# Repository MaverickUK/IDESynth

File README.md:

<h3 align="center">The sound of real mechanical drives, for retro PCs that use solid-state storage</h3>

<p align="center">

</p>

**Status:** Currently with beta testers with planned public release in early 2027

<!-- Demo: replace the photo with a short video of the board in a PC, spinning up and seeking (GIF in the README, linking to the MP4). -->

## Features

- **Real drives, sampled:** spin-up at power on, the idle hum, access clicks and crackles and the spindown when the power goes, played from the board's supercapacitor. Swap sample packs to change the drive.
- **Drives modelled from physics:** a pack can be a synthesised drive instead of recordings, from a 1985 stepper to a 2005 7,200 rpm drive, tuned by ear in the online [Drive Lab](https://maverickuk.github.io/IDESynth/drive-lab/).
- **Knows what the drive is doing:** from the motherboard's HDD LED, from your modern computer over USB or exactly from an [IDE Synth Bay](https://github.com/MaverickUK/IDESynthBay): file copies sound different from random access, and the head goes where the PC really reads.
- **On the board:** volume and balance on a knob, a button for the next pack, an RGB activity light and an optional OLED screen.

## Quick start

1. **Flash the firmware:** download `.uf2` from the [latest release](https://github.com/MaverickUK/IDESynth/releases/latest), hold **BOOT** and tap **RESET**, then drag the file onto the `RP2350` drive that appears.
2. **Fill a microSD card:** put each sample pack in its own folder under `/samples` (packs are in [HDDSynth_Samples](https://github.com/MaverickUK/HDDSynth_Samples)) and put the card in the board.
3. **Fit it:** connect the motherboard's HDD LED header to the board's HDD LED input and power
4. **Turn the PC on:** the drive spins up. Press the action button for the next pack.

## Documentation

| Page | What it covers |
|---|---|
| [SD card setup](docs/sd-card.md) | Sample packs, WAV formats, `pack.json` and every `settings.json` key |
| [Synthesised drives](docs/modelled-drives.md) | `drive.json`: synthesised drives, presets and every parameter |
| [Controls, lights and screen](docs/controls.md) | The rotary encoder and action button, beeps and LED colours, the OLED, editing the card over USB |
| [The IDE Synth Bay link](docs/link.md) | Wiring and what the drive tells the synth: sequential transfers, head positions, its timing |
| [Companion app and protocol](docs/companion.md) | Your computer's disk activity over USB, and the serial sentences |
| [The hardware](docs/hardware.md) | The MK5 board, mounting, and the KiCad files |
| [How it works](docs/architecture.md) | The two cores, where each sound plays from, power loss |
| [Building and flashing](docs/building.md) | Building it yourself, tests, the serial console, versioning |
| [History](docs/history.md) | From breadboard to MK5, with the early videos |
| [Changelog](firmware/CHANGELOG.md) | Every release |

## The Synth family

- **IDE Synth** (this one): plays the sound of hard drives and optical drives, real drives sampled or modelled from physics, in step with the Bay
- [IDE Synth Bay](https://github.com/MaverickUK/IDESynthBay): an IDE hard disk and CD-ROM drive served from a microSD card, telling the IDE Synth exactly what it does
- [FDD Synth Duo](https://github.com/MaverickUK/FDDSynthDuo): two floppy drives served from a microSD card, with real drive sounds
- [SynthMinder](https://github.com/MaverickUK/SynthMinder): the synth controller for DOS, changing discs, sound packs and the volume from the PC they're fitted to
- [GameMinder](https://github.com/MaverickUK/GameMinder): the games launcher for DOS, which browses, launches and keeps track of your DOS games
- [HDDSynth_Samples](https://github.com/MaverickUK/HDDSynth_Samples): the sample packs

## Licence and credits

- **Software and firmware:** [GNU GPL v3.0](LICENSE).
- **Hardware designs** (schematics, PCB files, BOM): [CC BY-NC-SA 4.0](LICENSE-HARDWARE), free for personal, non-commercial use and changes; commercial use needs my permission.

Inspired by the [HDD Clicker](https://www.serdashop.com/HDDClicker). Thanks to [Ian Scott of PicoGUS](https://picog.us/) for sharing his knowledge of the Pico on the ISA bus, [Marten Electric](https://www.martenelectric.cz/) for their ISA prototyping boards, and [PCBWay](https://www.pcbway.com) for making and assembling the prototypes.

Peter Bridger · [strifestreams.com/hddsynth](https://www.strifestreams.com/hddsynth)

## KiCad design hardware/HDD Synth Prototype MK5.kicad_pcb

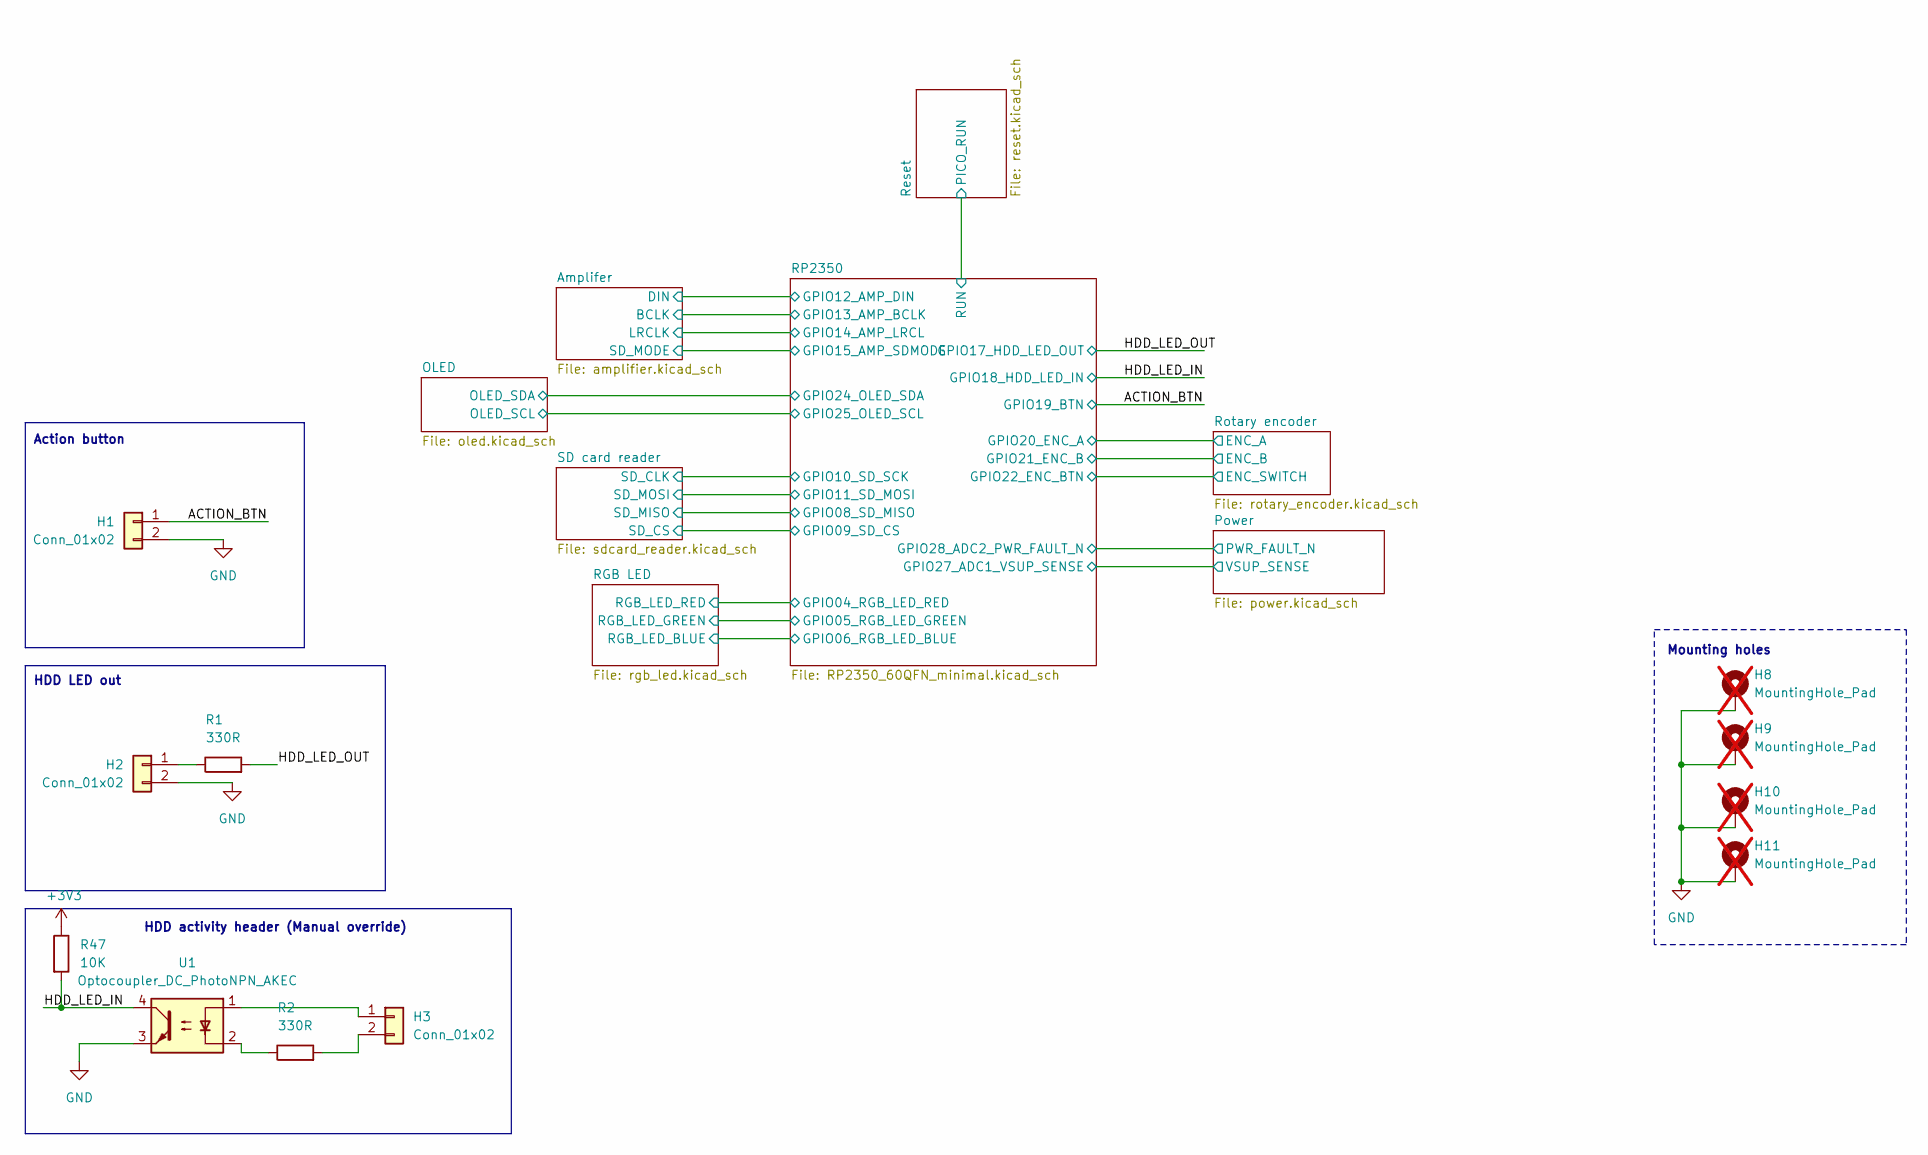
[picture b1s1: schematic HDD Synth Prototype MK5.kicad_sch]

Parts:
H1, H2, H3: Conn_01x02; PinHeader_1x02_P2.54mm_Vertical; LCSC Part Number C124375
H8, H9, H10, H11: MountingHole_Pad; MountingHole_3.2mm_M3_Pad; not fitted
R1, R2: 330R; R_0603_1608Metric; Manufacturer_Part_Number RC0603FR-07330RL; LCSC Part Number C23138
R47: 10K; R_0402_1005Metric; LCSC Part Number C25744
U1: Optocoupler_DC_PhotoNPN_AKEC; SO-4_4.4x3.6mm_P2.54mm; Manufacturer_Part_Number EL357N(C)(TA)-VG; LCSC Part Number C42381015

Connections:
/ACTION_BTN: H1.1; also elsewhere on the board
/HDD_LED_IN: R47.2, U1.4; also elsewhere on the board
GND: H1.2, H2.2, H8.1 (1_1), H9.1 (1_1), H10.1 (1_1), H11.1 (1_1), U1.3; also elsewhere on the board
unnamed: H3.1, U1.1
unnamed: H3.2, R2.2
unnamed: R2.1, U1.2

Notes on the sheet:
Action button
Mounting holes
HDD activity header (Manual override)
HDD LED out

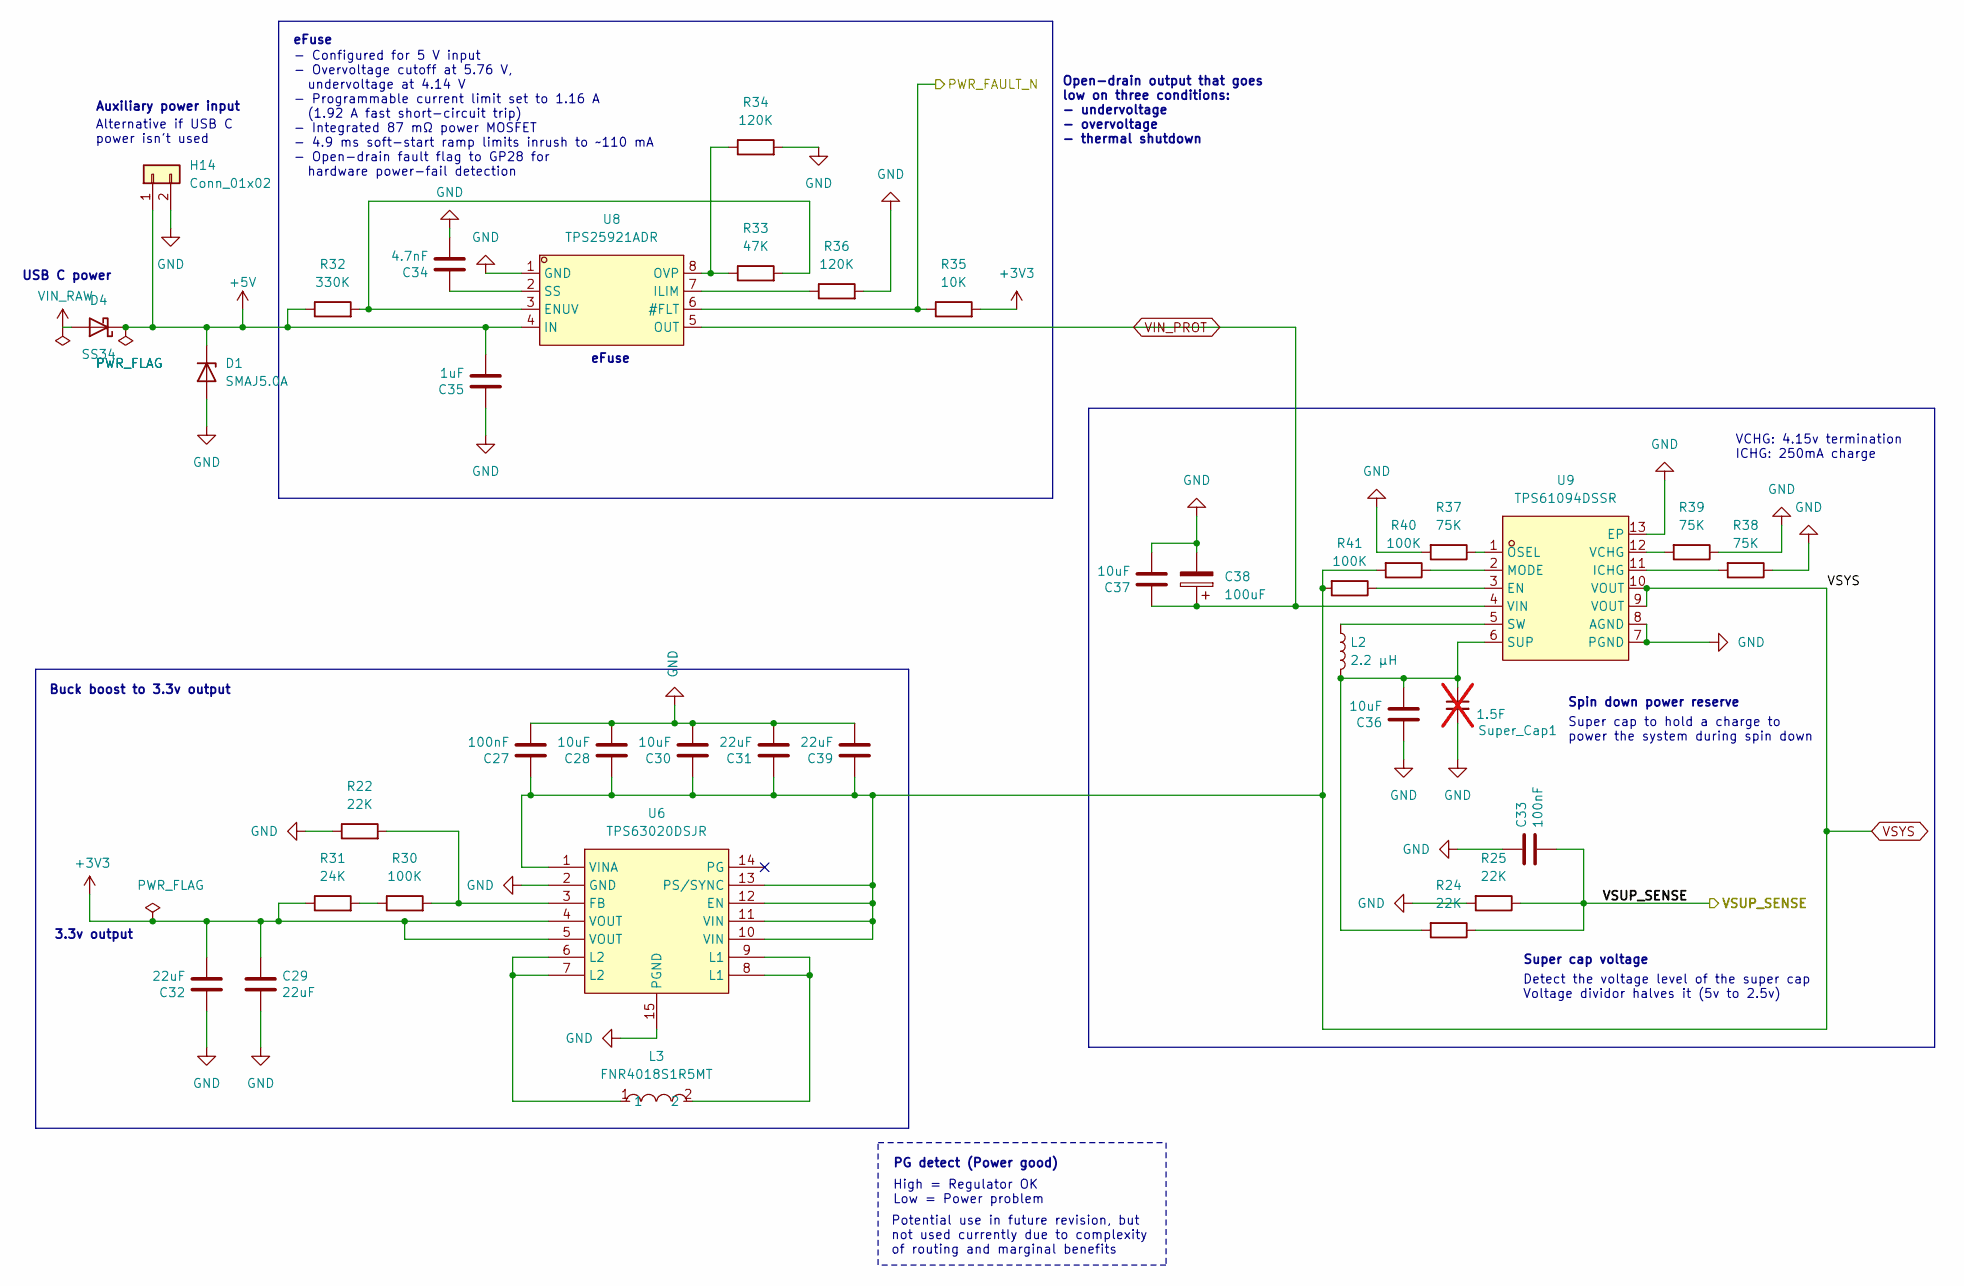
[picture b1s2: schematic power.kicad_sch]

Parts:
C27, C33: 100nF; C_0402_1005Metric; LCSC Part Number C1525
C28, C30, C36, C37: 10uF; C_0805_2012Metric; LCSC Part Number C15850
C29, C31, C32, C39: 22uF; C_0805_2012Metric; LCSC Part Number C45783
C34: 4.7nF; C_0402_1005Metric; LCSC Part Number C1538
C35: 1uF; C_0402_1005Metric; LCSC Part Number C52923
C38: 100uF; CP_Elec_6.3x7.7; LCSC Part Number C134801
D1: SMAJ5.0A; D_SMA; LCSC Part Number C113952
D4: SS34; D_SMA; LCSC Part Number C8678
H14: Conn_01x02; PinHeader_1x02_P2.54mm_Vertical; LCSC Part Number C124375
L2: 2.2 µH; IND-SMD_L4.0-W4.0_FNR40XXS; LCSC Part Number C167804
L3: FNR4018S1R5MT; IND-SMD_L4.0-W4.0_FNR40XXS; MPN FNR4018S1R5MT; LCSC Part Number C167802
R22: 22K; R_0402_1005Metric; LCSC Part Number C25768
R24, R25: 22K; R_0402_1005Metric; Manufacturer_Part_Number 0402WGF2202TCE; LCSC Part Number C25768
R30, R40, R41: 100K; R_0402_1005Metric; LCSC Part Number C25741
R31: 24K; R_0402_1005Metric; LCSC Part Number C25769
R32: 330K; R_0402_1005Metric; LCSC Part Number C25778
R33: 47K; R_0402_1005Metric; LCSC Part Number C25792
R34, R36: 120K; R_0402_1005Metric; LCSC Part Number C25750
R35: 10K; R_0402_1005Metric; LCSC Part Number C25744
R37, R38, R39: 75K; R_0402_1005Metric; LCSC Part Number C25798
Super_Cap1: 1.5F; SuperCap_Eaton_PHV_9.0x17.3mm_P11.80mm; not fitted
U6: TPS63020DSJR; VSON-14_L4.0-W3.0-P0.50-BL-EP_TI_DSJ; MPN TPS63020DSJR; LCSC Part Number C15483
U8: TPS25921ADR; SOIC-8_L5.0-W4.0-P1.27-LS6.0-BL; MPN TPS25921ADR; LCSC Part Number C189199
U9: TPS61094DSSR; WSON-12_L3.0-W2.0-P0.5-BL-EP; MPN TPS61094DSSR; LCSC Part Number C3034939

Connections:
+5V: C35.2, D1.1 (K), D4.1 (K), H14.1, R32.1, U8.4 (IN); also elsewhere on the board
/Power/VSUP_SENSE: C33.2, R24.1, R25.1; also elsewhere on the board
/RP2350/PWR_FAULT_N: R35.1, U8.6 (#FLT); also elsewhere on the board
GND: C27.2, C28.2, C29.2, C30.2, C31.2, C32.1, C33.1, C34.2, C35.1, C36.1, C37.2, C38.2, C39.2, D1.2 (A), H14.2, R22.1, R25.2, R34.2, R36.2, R37.2, R38.1, R39.1, Super_Cap1.2, U6.2 (GND), U6.15 (PGND), U8.1 (GND), U9.7 (PGND), U9.8 (AGND), U9.13 (EP); also elsewhere on the board
unnamed: L3.1, U6.6 (L2), U6.7 (L2)
unnamed: L3.2, U6.8 (L1), U6.9 (L1)
unnamed: R30.1, R31.2
unnamed: R22.2, R30.2, U6.3 (FB)
unnamed: R32.2, R33.2, U8.3 (ENUV)
unnamed: R36.1, U8.7 (ILIM)
unnamed: R33.1, R34.1, U8.8 (OVP)
unnamed: C34.1, U8.2 (SS)
unnamed: R41.1, U9.3 (EN)
unnamed: R38.2, U9.11 (ICHG)
unnamed: R40.1, U9.2 (MODE)
unnamed: R37.1, U9.1 (OSEL)
unnamed: C36.2, L2.2, R24.2, Super_Cap1.1, U9.6 (SUP)
unnamed: L2.1, U9.5 (SW)
unnamed: R39.2, U9.12 (VCHG)
VIN_PROT: C37.1, C38.1, U8.5 (OUT), U9.4 (VIN); also elsewhere on the board
VIN_RAW: D4.2 (A); also elsewhere on the board
VSYS: C27.1, C28.1, C30.1, C31.1, C39.1, R40.2, R41.2, U6.1 (VINA), U6.10 (VIN), U6.11 (VIN), U6.12 (EN), U6.13 (PS/SYNC), U9.9 (VOUT), U9.10 (VOUT); also elsewhere on the board

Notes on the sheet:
Potential use in future revision, but not used currently due to complexity of routing and marginal benefits
- Configured for 5 V input - Overvoltage cutoff at 5.76 V, undervoltage at 4.14 V - Programmable current limit set to 1.16 A (1.92 A fast short-circuit trip) - Integrated 87 mΩ power MOSFET - 4.9 ms soft-start ramp limits inrush to ~110 mA - Open-drain fault flag to GP28 for hardware power-fail det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
Alternative if USB C power isn't used
VCHG: 4.15v termination ICHG: 250mA charge
Super cap to hold a charge to power the system during spin down
eFuse
3.3v output
Open-drain output that goes low on three conditions: - undervoltage - overvoltage - thermal shutdown
Super cap voltage
PG detect (Power good)
Buck boost to 3.3v output
Spin down power reserve
High = Regulator OK Low = Power problem
USB C power
Detect the voltage level of the super cap Voltage dividor halves it (5v to 2.5v)
Auxiliary power input

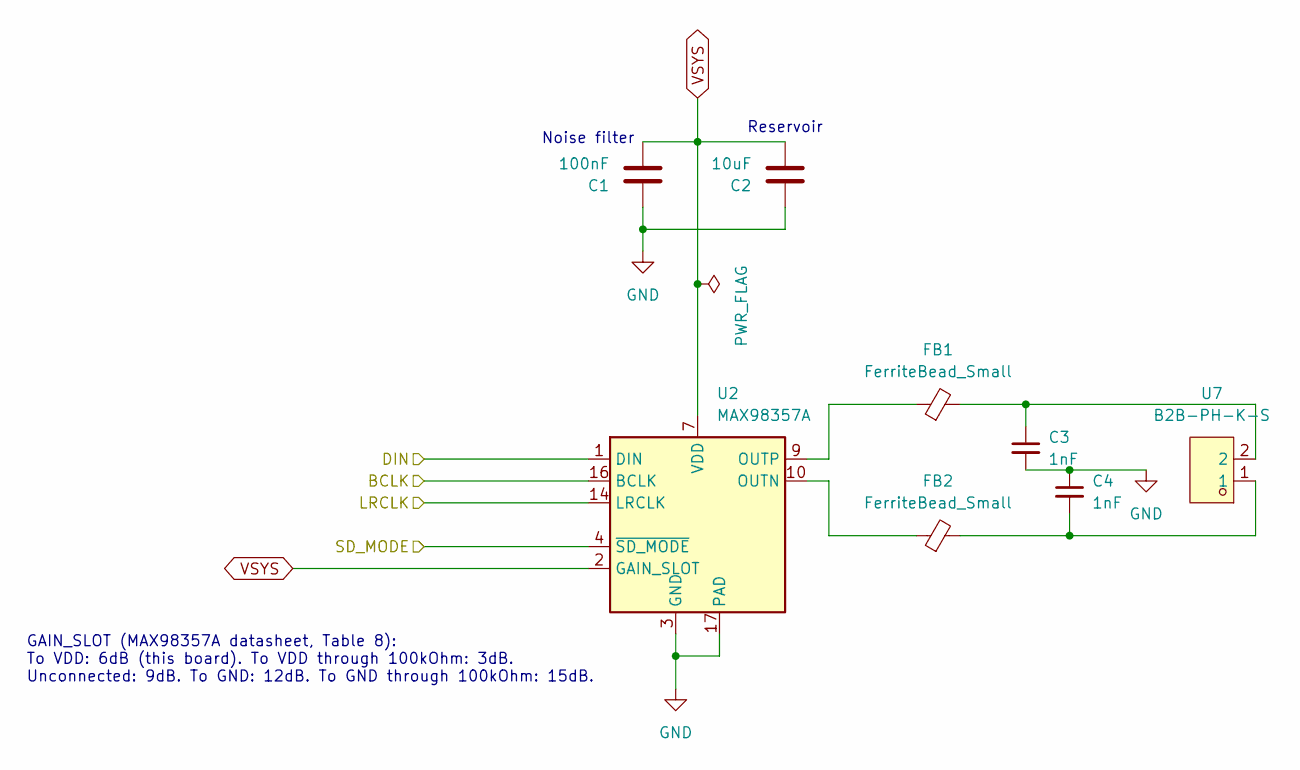
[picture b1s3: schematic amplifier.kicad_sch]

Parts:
C1: 100nF; C_0402_1005Metric; Manufacturer_Part_Number CL05B104KO5NNNC; LCSC Part Number C1525
C2: 10uF; C_1206_3216Metric; Manufacturer_Part_Number CL31A106KAHNNNE; LCSC Part Number C13585
C3, C4: 1nF; C_0603_1608Metric; Manufacturer_Part_Number 0603B102K500NT; LCSC Part Number C1588
FB1, FB2: FerriteBead_Small; L_0805_2012Metric; Manufacturer_Part_Number BLM21PG221SN1D; LCSC Part Number C85840
U2: MAX98357A; TQFN-16-1EP_3x3mm_P0.5mm_EP1.23x1.23mm; Manufacturer_Part_Number MAX98357AETE+T; LCSC Part Number C910544
U7: B2B-PH-K-S; JST_PH_B2B-PH-K_1x02_P2.00mm_Vertical; MPN B2B-PH-K-S(LF)(SN); LCSC Part Number C131337

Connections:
/RP2350/AMP_BCLK: U2.16 (BCLK); also elsewhere on the board
/RP2350/AMP_DIN: U2.1 (DIN); also elsewhere on the board
/RP2350/AMP_LRCL: U2.14 (LRCLK); also elsewhere on the board
/RP2350/AMP_SDMODE: U2.4 (~SD_MODE); also elsewhere on the board
GND: C1.1, C2.1, C3.2, C4.1, U2.3 (GND), U2.11 (GND), U2.15 (GND), U2.17 (PAD); also elsewhere on the board
unnamed: C3.1, FB1.2, U7.2
unnamed: C4.2, FB2.2, U7.1
unnamed: FB2.1, U2.10 (OUTN)
unnamed: FB1.1, U2.9 (OUTP)
VSYS: C1.2, C2.2, U2.2 (GAIN_SLOT), U2.7 (VDD), U2.8 (VDD); also elsewhere on the board

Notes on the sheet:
GAIN_SLOT (MAX98357A datasheet, Table 8): To VDD: 6dB (this board). To VDD through 100kOhm: 3dB. Unconnected: 9dB. To GND: 12dB. To GND through 100kOhm: 15dB.
Reservoir
Noise filter

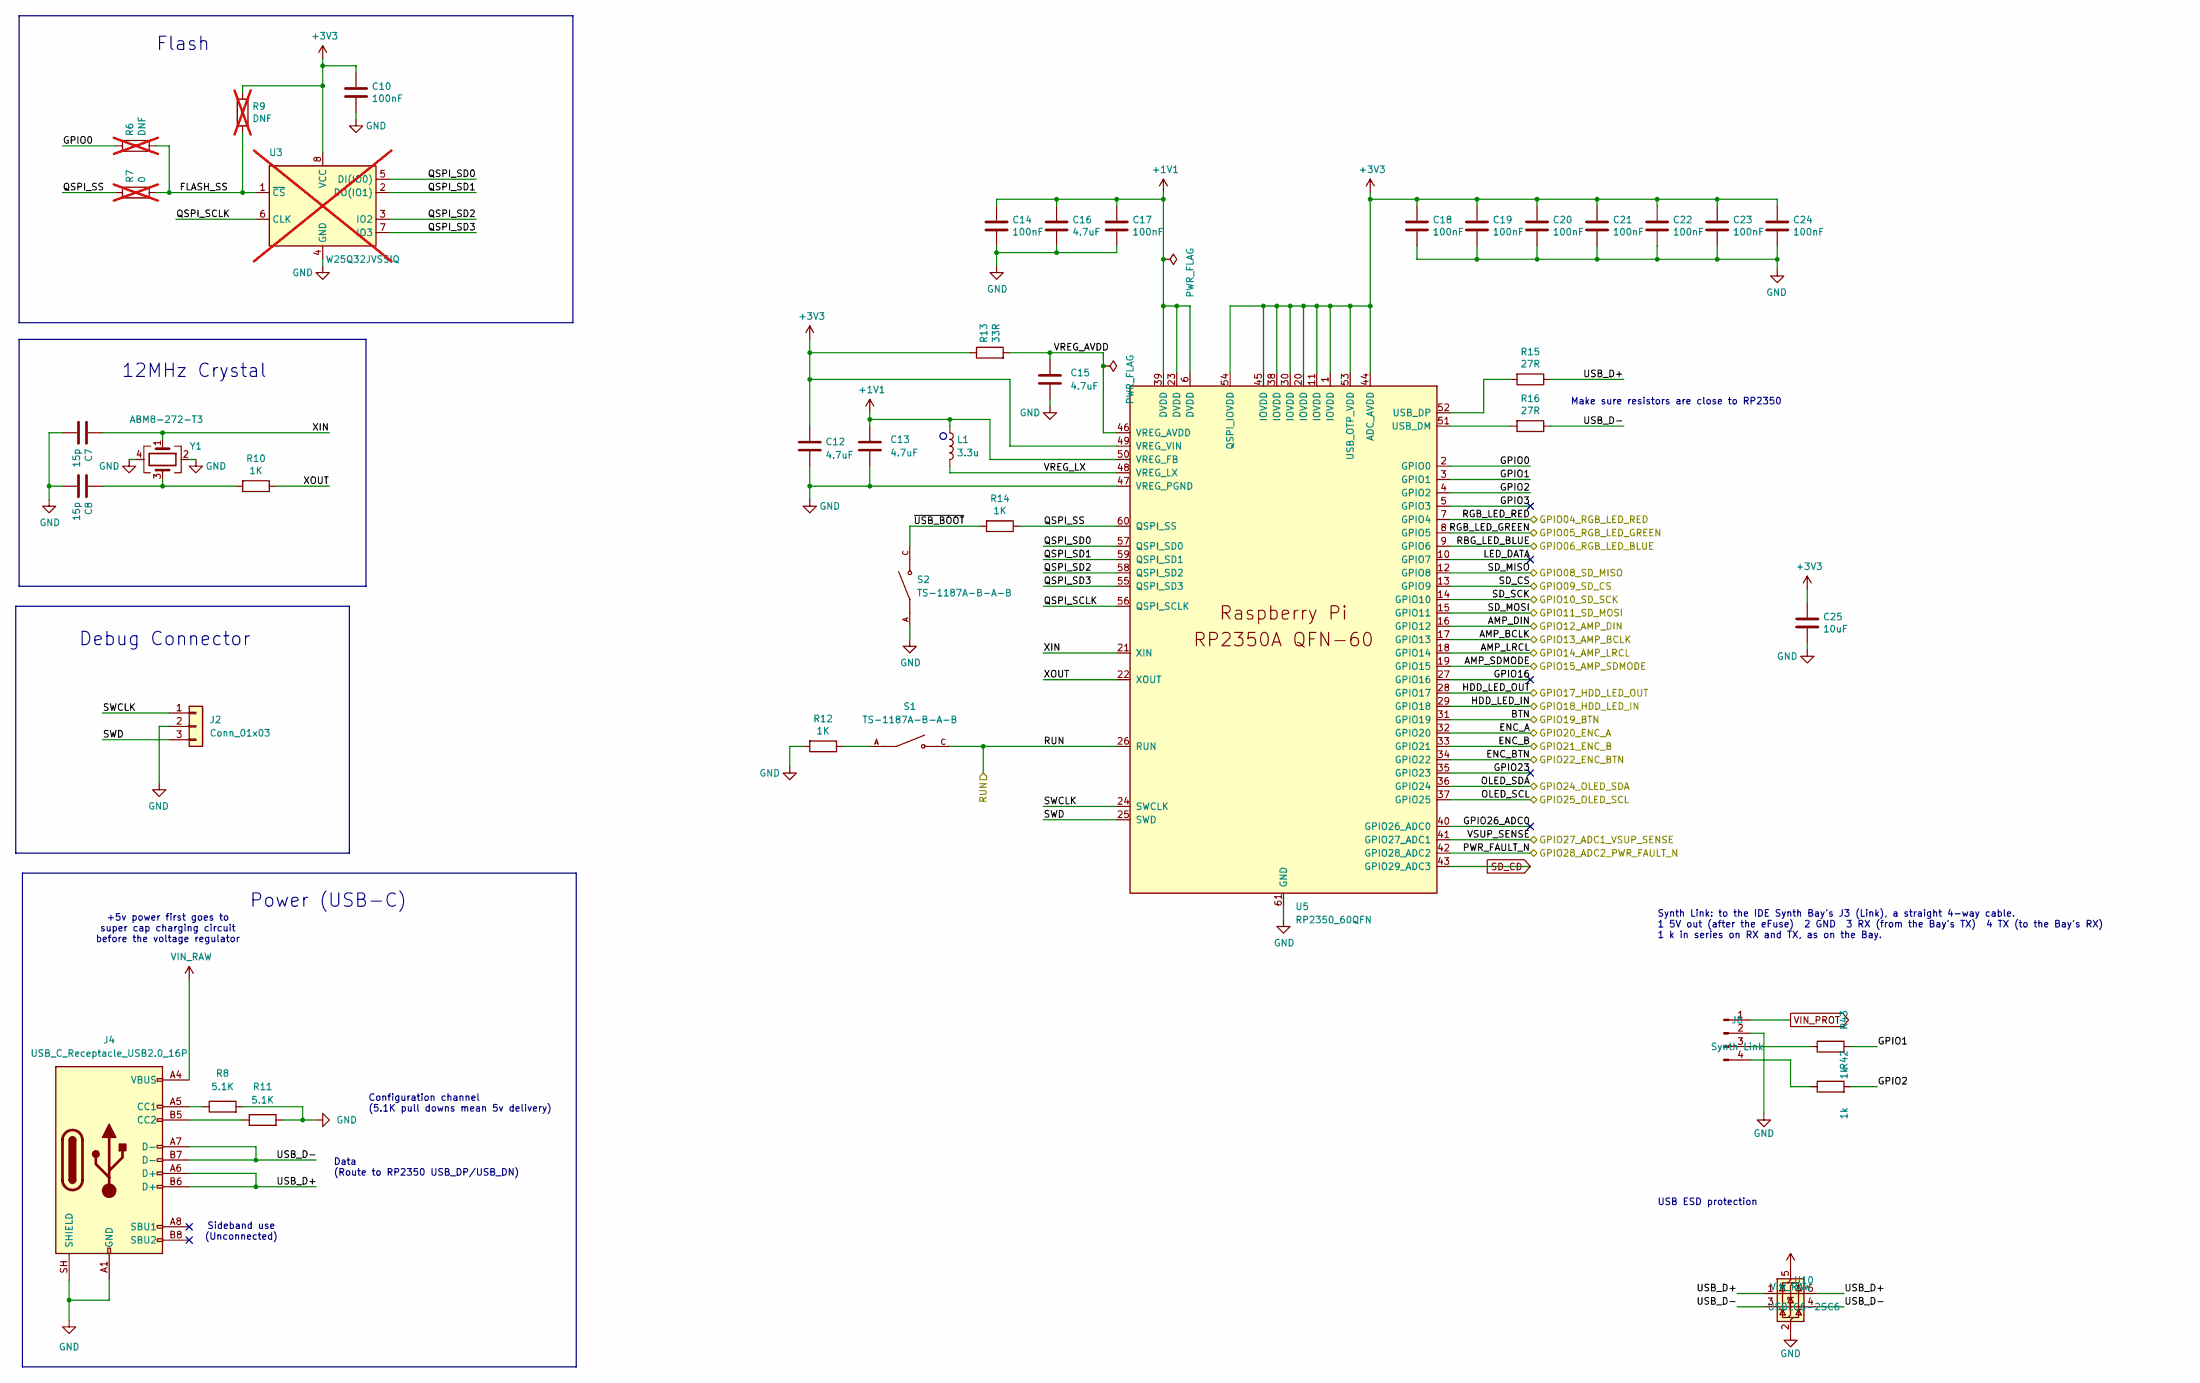
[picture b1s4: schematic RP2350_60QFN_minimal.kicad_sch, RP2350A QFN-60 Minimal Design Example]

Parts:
C7, C8: 15p; C_0402_1005Metric; LCSC Part Number C1548
C10, C14, C17, C18, C19, C20, C21, C22, C23, C24: 100nF; C_0402_1005Metric; LCSC Part Number C1525
C12, C13: 4.7uF; C_0402_1005Metric_small_pads; LCSC Part Number C23733
C15, C16: 4.7uF; C_0402_1005Metric; LCSC Part Number C23733
C25: 10uF; C_0805_2012Metric; LCSC Part Number C15850
J2: Conn_01x03; PinHeader_1x03_P2.54mm_Vertical; LCSC Part Number C49257
J4: USB_C_Receptacle_USB2.0_16P; USB_C_Receptacle_HRO_TYPE-C-31-M-12; LCSC Part Number C165948
J8: Synth Link; PinHeader_1x04_P2.54mm_Vertical; LCSC Part Number C124378
L1: 3.3u; L_pol_2016; LCSC Part Number C42411119
R6, R9: DNF; R_0402_1005Metric; not fitted
R7: 0; R_0402_1005Metric; LCSC Part Number C17168; not fitted
R8, R11: 5.1K; R_0402_1005Metric; LCSC Part Number C25905
R10, R12, R14: 1K; R_0402_1005Metric; LCSC Part Number C11702
R13: 33R; R_0402_1005Metric; LCSC Part Number C25105
R15, R16: 27R; R_0402_1005Metric; LCSC Part Number C25100
R42, R43: 1k; R_0402_1005Metric; LCSC Part Number C11702
S1, S2: TS-1187A-B-A-B; SW_TS-1187A-B-A-B; PARTREV A0; LCSC Part Number C318884
U3: W25Q32JVSSIQ; SOIC-8_5.23x5.23mm_P1.27mm; LCSC Part Number C179173; not fitted
U5: RP2350_60QFN; RP2350-QFN-60-1EP_7x7_P0.4mm_EP3.4x3.4mm_ThermalVias; LCSC Part Number C41378174
U10: USBLC6-2SC6; SOT-23-6; MPN USBLC6-2SC6; LCSC Part Number C7519
Y1: ABM8-272-T3; Crystal_SMD_3225-4Pin_3.2x2.5mm; LCSC Part Number C20617575

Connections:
+1V1: C13.1, C14.1, C16.1, C17.1, L1.1, U5.6 (DVDD), U5.23 (DVDD), U5.39 (DVDD), U5.50 (VREG_FB)
/ACTION_BTN: U5.31 (GPIO19); also elsewhere on the board
/HDD_LED_IN: U5.29 (GPIO18); also elsewhere on the board
/Power/VSUP_SENSE: U5.41 (GPIO27_ADC1); also elsewhere on the board
/RP2350/AMP_BCLK: U5.17 (GPIO13); also elsewhere on the board
/RP2350/AMP_DIN: U5.16 (GPIO12); also elsewhere on the board
/RP2350/AMP_LRCL: U5.18 (GPIO14); also elsewhere on the board
/RP2350/AMP_SDMODE: U5.19 (GPIO15); also elsewhere on the board
/RP2350/ENC_A: U5.32 (GPIO20); also elsewhere on the board
/RP2350/ENC_B: U5.33 (GPIO21); also elsewhere on the board
/RP2350/ENC_BTN: U5.34 (GPIO22); also elsewhere on the board
/RP2350/GPIO0: U5.2 (GPIO0)
/RP2350/GPIO1: R43.2, U5.3 (GPIO1)
/RP2350/GPIO2: R42.2, U5.4 (GPIO2)
/RP2350/GPIO3: U5.5 (GPIO3)
/RP2350/GPIO16: U5.27 (GPIO16)
/RP2350/GPIO23: U5.35 (GPIO23)
/RP2350/GPIO26_ADC0: U5.40 (GPIO26_ADC0)
/RP2350/LED_DATA: U5.10 (GPIO7)
/RP2350/OLED_SCL: U5.37 (GPIO25); also elsewhere on the board
/RP2350/OLED_SDA: U5.36 (GPIO24); also elsewhere on the board
/RP2350/PWR_FAULT_N: U5.42 (GPIO28_ADC2); also elsewhere on the board
/RP2350/QSPI_SCLK: U3.6 (CLK), U5.56 (QSPI_SCLK); also elsewhere on the board
/RP2350/QSPI_SD0: U3.5 (DI(IO0)), U5.57 (QSPI_SD0); also elsewhere on the board
/RP2350/QSPI_SD1: U3.2 (DO(IO1)), U5.59 (QSPI_SD1); also elsewhere on the board
/RP2350/QSPI_SD2: U3.3 (IO2), U5.58 (QSPI_SD2); also elsewhere on the board
/RP2350/QSPI_SD3: U3.7 (IO3), U5.55 (QSPI_SD3); also elsewhere on the board
/RP2350/RBG_LED_BLUE: U5.9 (GPIO6); also elsewhere on the board
/RP2350/RGB_LED_GREEN: U5.8 (GPIO5); also elsewhere on the board
/RP2350/RGB_LED_RED: U5.7 (GPIO4); also elsewhere on the board
/RP2350/RUN: S1.C, S1.D, U5.26 (RUN); also elsewhere on the board
/RP2350/SD_CS: U5.13 (GPIO9); also elsewhere on the board
/RP2350/SD_MISO: U5.12 (GPIO8); also elsewhere on the board
/RP2350/SD_MOSI: U5.15 (GPIO11); also elsewhere on the board
/RP2350/SD_SCK: U5.14 (GPIO10); also elsewhere on the board
/RP2350/SWCLK: J2.1, U5.24 (SWCLK)
/RP2350/SWD: J2.3, U5.25 (SWD)
/RP2350/USB_D+: J4.A6 (D+), J4.B6 (D+), R15.1, U10.1 (I/O1), U10.6 (I/O1)
/RP2350/USB_D-: J4.A7 (D-), J4.B7 (D-), R16.1, U10.3 (I/O2), U10.4 (I/O2)
/RP2350/VREG_AVDD: C15.1, R13.2, U5.46 (VREG_AVDD)
/RP2350/VREG_LX: L1.2, U5.48 (VREG_LX)
/RP2350/XIN: C7.1, U5.21 (XIN), Y1.1
/RP2350/~USB_BOOT: R14.2, S2.C, S2.D
GND: C7.2, C8.2, C10.2, C12.2, C13.2, C14.2, C15.2, C16.2, C17.2, C18.2, C19.2, C20.2, C21.2, C22.2, C23.2, C24.2, C25.2, J2.2, J4.A1 (GND), J4.A12 (GND), J4.B1 (GND), J4.B12 (GND), J4.SH (SHIELD), J8.2, R8.2, R11.2, R12.2, S2.A, S2.B, U5.47 (VREG_PGND), U5.61 (GND), U10.2 (GND), Y1.2, Y1.4; also elsewhere on the board
unnamed: J4.A5 (CC1), R8.1
unnamed: J4.B5 (CC2), R11.1
unnamed: J8.3, R43.1
unnamed: J8.4, R42.1
unnamed: R12.1, S1.A, S1.B
unnamed: R16.2, U5.51 (USB_DM)
unnamed: R15.2, U5.52 (USB_DP)
SD_CD: U5.43 (GPIO29_ADC3); also elsewhere on the board
VIN_PROT: J8.1; also elsewhere on the board
VIN_RAW: J4.A4 (VBUS), J4.A9 (VBUS), J4.B4 (VBUS), J4.B9 (VBUS), U10.5 (VBUS); also elsewhere on the board

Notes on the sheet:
+5v power first goes to super cap charging circuit before the voltage regulator
Debug Connector
Configuration channel (5.1K pull downs mean 5v delivery)
Flash
Data (Route to RP2350 USB_DP/USB_DN)
Make sure resistors are close to RP2350
12MHz Crystal
Power (USB-C)
Sideband use (Unconnected)
Synth Link: to the IDE Synth Bay's J3 (Link), a straight 4-way cable. 1 5V out (after the eFuse) 2 GND 3 RX (from the Bay's TX) 4 TX (to the Bay's RX) 1 k in series on RX and TX, as on the Bay.
USB ESD protection

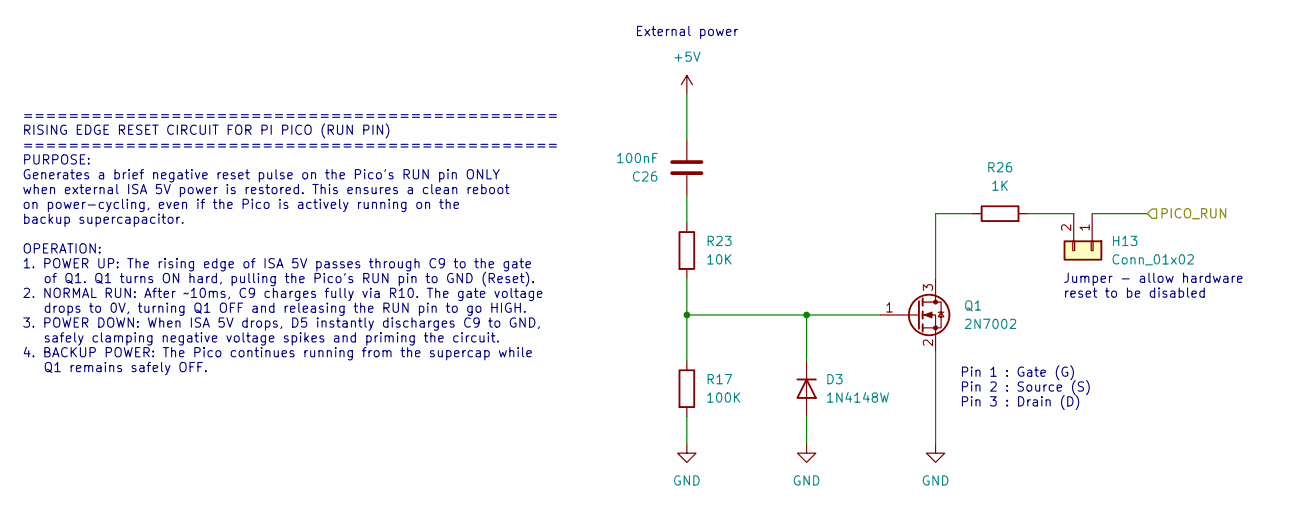
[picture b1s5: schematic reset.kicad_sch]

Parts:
C26: 100nF; C_0402_1005Metric; Manufacturer_Part_Number CL05B104KO5NNNC; LCSC Part Number C1525
D3: 1N4148W; D_SOD-123; LCSC Part Number C81598
H13: Conn_01x02; PinHeader_1x02_P2.54mm_Vertical; LCSC Part Number C124375
Q1: 2N7002; SOT-23; LCSC Part Number C8545
R17: 100K; R_0402_1005Metric; LCSC Part Number C25741
R23: 10K; R_0402_1005Metric; LCSC Part Number C25744
R26: 1K; R_0402_1005Metric; LCSC Part Number C11702

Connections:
+5V: C26.2; also elsewhere on the board
/RP2350/RUN: H13.1; also elsewhere on the board
GND: D3.2 (A), Q1.2 (S), R17.2; also elsewhere on the board
unnamed: C26.1, R23.1
unnamed: D3.1 (K), Q1.1 (G), R17.1, R23.2
unnamed: H13.2, R26.2
unnamed: Q1.3 (D), R26.1

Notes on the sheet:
Jumper - allow hardware reset to be disabled
=============================================== RISING EDGE RESET CIRCUIT FOR PI PICO (RUN PIN) =============================================== PURPOSE: Generates a brief negative reset pulse on the Pico's RUN pin ONLY when external ISA 5V power is restored. This ensures a clean reboot on power-cyc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
Pin 1 : Gate (G) Pin 2 : Source (S) Pin 3 : Drain (D)
External power

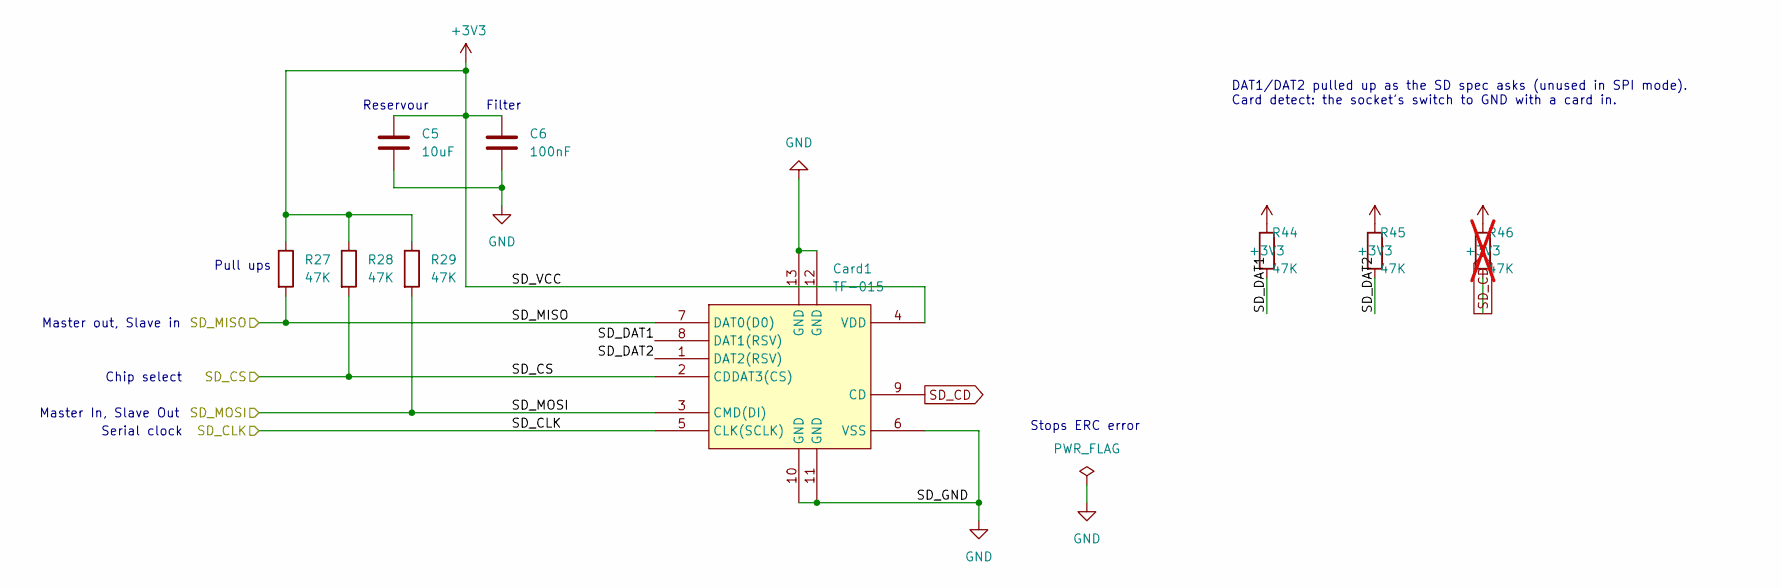
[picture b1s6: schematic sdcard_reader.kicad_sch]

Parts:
C5: 10uF; C_1206_3216Metric; Manufacturer_Part_Number CL31A106KAHNNNE; LCSC Part Number C13585
C6: 100nF; C_0402_1005Metric; Manufacturer_Part_Number CL05B104KO5NNNC; LCSC Part Number C1525
Card1: TF-015; TF-SMD_TF-015; MPN TF-015; LCSC Part Number C113206
R27, R28, R29, R44, R45: 47K; R_0402_1005Metric; LCSC Part Number C25792
R46: 47K; R_0402_1005Metric; LCSC Part Number C25792; not fitted

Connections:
/RP2350/SD_CS: Card1.2 (CDDAT3(CS)), R28.2; also elsewhere on the board
/RP2350/SD_MISO: Card1.7 (DAT0(D0)), R27.2; also elsewhere on the board
/RP2350/SD_MOSI: Card1.3 (CMD(DI)), R29.2; also elsewhere on the board
/RP2350/SD_SCK: Card1.5 (CLK(SCLK)); also elsewhere on the board
/SD card reader/SD_DAT1: Card1.8 (DAT1(RSV)), R44.2
/SD card reader/SD_DAT2: Card1.1 (DAT2(RSV)), R45.2
GND: C5.2, C6.2, Card1.6 (VSS), Card1.10 (GND), Card1.11 (GND), Card1.12 (GND), Card1.13 (GND); also elsewhere on the board
SD_CD: Card1.9 (CD), R46.2; also elsewhere on the board

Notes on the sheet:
Stops ERC error
Master In, Slave Out
Pull ups
Filter
Chip select
Master out, Slave in
Reservour
Serial clock
DAT1/DAT2 pulled up as the SD spec asks (unused in SPI mode). Card detect: the socket's switch to GND with a card in.

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
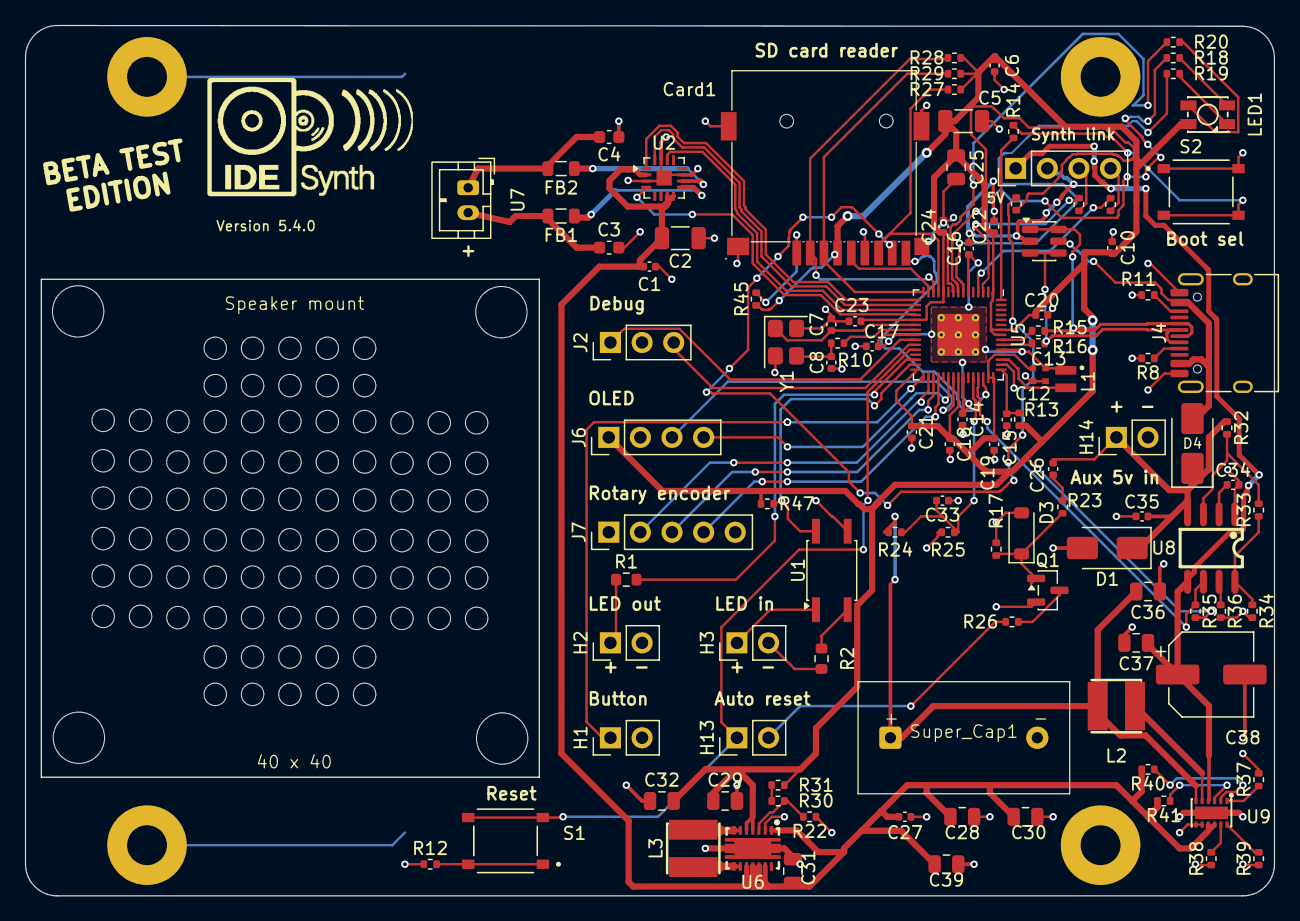
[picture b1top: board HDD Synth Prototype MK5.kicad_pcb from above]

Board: 2 copper layers, 100.3 x 69.9 mm, 114 parts (1 on the bottom side), 82 nets.

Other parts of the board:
 : LOGO; MHDDLA_Sound_40mm
J6: Conn_01x04_Pin; PinHeader_1x04_P2.54mm_Vertical
J7: Conn_01x05; PinHeader_1x05_P2.54mm_Vertical
LED1: XL-3528RGBW-HM; LED-SMD_4P-L3.2-W2.8-LS3.5-XL-3528RGBW-HM5
R18, R20: 33R; R_0402_1005Metric
R19: 200R; R_0402_1005Metric

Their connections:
/RP2350/ENC_A: J7.2; also elsewhere on the board
/RP2350/ENC_B: J7.3; also elsewhere on the board
/RP2350/ENC_BTN: J7.4; also elsewhere on the board
/RP2350/OLED_SCL: J6.3; also elsewhere on the board
/RP2350/OLED_SDA: J6.4; also elsewhere on the board
/RP2350/RBG_LED_BLUE: R20.1; also elsewhere on the board
/RP2350/RGB_LED_GREEN: R18.1; also elsewhere on the board
/RP2350/RGB_LED_RED: R19.1; also elsewhere on the board
GND: J6.2, J7.1, J7.5; also elsewhere on the board
unnamed: LED1.4 (B-), R20.2
unnamed: LED1.3 (G-), R18.2
unnamed: LED1.1 (R-), R19.2

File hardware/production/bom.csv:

Designator,Footprint,Quantity,Value,LCSC Part #
"C1, C10, C14, C17, C18, C19, C20, C21, C22, C23, C24, C26, C27, C33, C6",0402,15,100nF,C1525
"C12, C13, C15, C16",0402,4,4.7uF,C23733
"C2, C5",1206,2,10uF,C13585
"C25, C28, C30, C36, C37",0805,5,10uF,C15850
"C29, C31, C32, C39",0805,4,22uF,C45783
"C3, C4",0603,2,1nF,C1588
C34,0402,1,4.7nF,C1538
C35,0402,1,1uF,C52923
C38,CP_Elec_6.3x7.7,1,100uF,C134801
"C7, C8",0402,2,15p,C1548
CARD1,TF-SMD_TF-015,1,TF-015,C113206
D1,D_SMA,1,SMAJ5.0A,C113952
D3,D_SOD-123,1,1N4148W,C81598
D4,D_SMA,1,SS34,C8678
"FB1, FB2",0805,2,FerriteBead_Small,C85840
"H1, H13, H14, H2, H3",PinHeader_1x02_P2.54mm_Vertical,5,Conn_01x02,C124375
J2,PinHeader_1x03_P2.54mm_Vertical,1,Conn_01x03,C49257
J4,USB_C_Receptacle_HRO_TYPE-C-31-M-12,1,USB_C_Receptacle_USB2.0_16P,C165948
J6,PinHeader_1x04_P2.54mm_Vertical,1,Conn_01x04_Pin,C124378
J7,PinHeader_1x05_P2.54mm_Vertical,1,Conn_01x05,C124379
J8,PinHeader_1x04_P2.54mm_Vertical,1,Synth Link,C124378
L1,L_pol_2016,1,3.3u,C42411119
L2,IND-SMD_L4.0-W4.0_FNR40XXS,1,2.2 µH,C167804
L3,IND-SMD_L4.0-W4.0_FNR40XXS,1,FNR4018S1R5MT,C167802
LED1,LED-SMD_4P-L3.2-W2.8-LS3.5-XL-3528RGBW-HM5,1,XL-3528RGBW-HM,C2843813
Q1,SOT-23,1,2N7002,C8545
"R1, R2",0603,2,330R,C23138
"R10, R12, R14, R26, R42, R43",0402,6,1K,C11702
"R11, R8",0402,2,5.1K,C25905
"R13, R18, R20",0402,3,33R,C25105
"R15, R16",0402,2,27R,C25100
"R17, R30, R40, R41",0402,4,100K,C25741
R19,0402,1,200R,C25087
"R22, R24, R25",0402,3,22K,C25768
"R23, R35, R47",0402,3,10K,C25744
"R27, R28, R29, R33, R44, R45",0402,6,47K,C25792
R31,0402,1,24K,C25769
R32,0402,1,330K,C25778
"R34, R36",0402,2,120K,C25750
"R37, R38, R39",0402,3,75K,C25798
"S1, S2",SW_TS-1187A-B-A-B,2,TS-1187A-B-A-B,C318884
U1,SO-4_4.4x3.6mm_P2.54mm,1,Optocoupler_DC_PhotoNPN_AKEC,C42381015
U10,SOT-23-6,1,USBLC6-2SC6,C7519
U2,TQFN-16-1EP_3x3mm_P0.5mm_EP1.23x1.23mm,1,MAX98357A,C910544
U5,RP2350-QFN-60-1EP_7x7_P0.4mm_EP3.4x3.4mm_ThermalVias,1,RP2350_60QFN,C41378174
U6,VSON-14_L4.0-W3.0-P0.50-BL-EP_TI_DSJ,1,TPS63020DSJR,C15483
U7,JST_PH_B2B-PH-K_1x02_P2.00mm_Vertical,1,B2B-PH-K-S,C131337
U8,SOIC-8_L5.0-W4.0-P1.27-LS6.0-BL,1,TPS25921ADR,C189199
U9,WSON-12_L3.0-W2.0-P0.5-BL-EP,1,TPS61094DSSR,C3034939
Y1,Crystal_SMD_3225-4Pin_3.2x2.5mm,1,ABM8-272-T3,C20617575
